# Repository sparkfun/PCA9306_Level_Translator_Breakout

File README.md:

PCA9306 Level Translator Breakout
=================================

[*PCA9306 Level Translator Breakout(BOB-15439)*](https://www.sparkfun.com/products/15439)

This is a breakout board for the PCA9306 dual bidirectional voltage-level translator. 

Repository Contents
-------------------
* **/Hardware** - Eagle design files for the board (.brd, .sch)

Documentation
--------------
* **[Hookup Guide](https://learn.sparkfun.com/tutorials/pca9306-logic-level-translator-hookup-guide-v2)** - Basic hookup guide for the PCA9306 logic level translator.
* **[Logic Levels](https://learn.sparkfun.com/tutorials/logic-levels)**
* **[SparkFun Fritzing repo](https://github.com/sparkfun/Fritzing_Parts)** - Fritzing diagrams for SparkFun products.

License Information
-------------------
The hardware is released under [Creative Commons Share-alike 3.0](http://creativecommons.org/licenses/by-sa/3.0/).

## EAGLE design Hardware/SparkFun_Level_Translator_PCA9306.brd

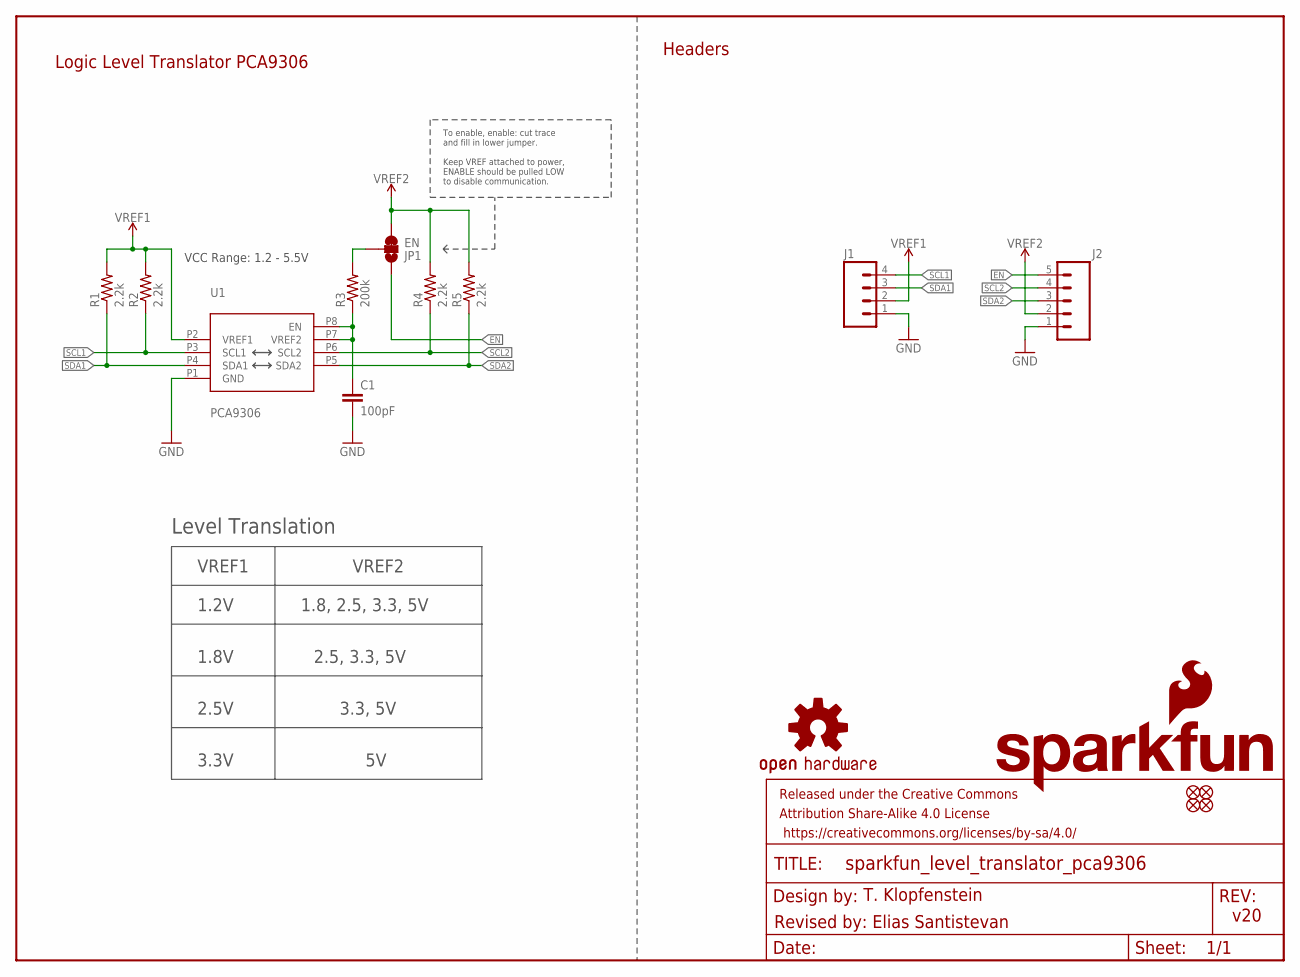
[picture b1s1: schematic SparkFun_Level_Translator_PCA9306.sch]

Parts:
C1: 100pF; 0603
FD1, FD2, FD3, FD4: FIDUCIALUFIDUCIAL; FIDUCIAL-MICRO
FRAME1: FRAME-LETTER; CREATIVE_COMMONS
J1: CONN_041X04_NO_SILK; 1X04_NO_SILK
J2: CONN_05NO_SILK; 1X05_NO_SILK
JP1: EN; SMT-JUMPER_3_1-NC_TRACE_SILK
LOGO1: OSHW-LOGOMINI; OSHW-LOGO-MINI
LOGO2: SFE_LOGO_NAME.1_INCH; SFE_LOGO_NAME_.1
LOGO3: SFE_LOGO_FLAME.1_INCH; SFE_LOGO_FLAME_.1
R1, R2, R4, R5: 2.2k; 0603
R3: 200k; 0603
U1: PCA9306; VSSOP_8PIN

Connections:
EN: J2.5, JP1.1
GND: C1.2, J1.1, J2.1, U1.P1 (GND)
JUMPER_IN: JP1.2, R3.2
SCL1: J1.4, R2.1, U1.P3 (SCL1)
SCL2: J2.4, R4.1, U1.P6 (SCL2)
SDA1: J1.3, R1.1, U1.P4 (SDA1)
SDA2: J2.3, R5.1, U1.P5 (SDA2)
VREF1: J1.2, R1.2, R2.2, U1.P2 (VREF1)
VREF2: J2.2, JP1.3, R4.2, R5.2
VREF2_IN: C1.1, R3.1, U1.P7 (VREF2), U1.P8 (EN)

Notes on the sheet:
T. Klopfenstein
v20
Logic Level Translator PCA9306
Headers
Revised by: Elias Santistevan
Level Translation
VREF1
VREF2
1.2V
1.8, 2.5, 3.3, 5V
1.8V
2.5, 3.3, 5V
2.5V
3.3, 5V
3.3V
VCC Range: 1.2 - 5.5V
To enable, enable: cut trace and fill in lower jumper.
Keep VREF attached to power, ENABLE should be pulled LOW to disable communication.

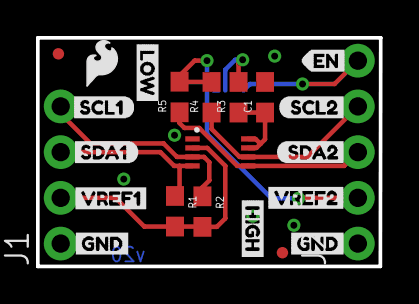
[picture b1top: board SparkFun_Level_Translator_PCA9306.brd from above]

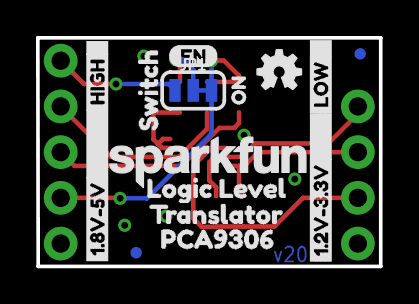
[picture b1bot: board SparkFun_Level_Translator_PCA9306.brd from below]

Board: 2 copper layers, 19.1 x 12.7 mm, 39 parts (15 on the bottom side), 10 nets.

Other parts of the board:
U$1: SWITCH1
U$2: VREF13
U$3: SCL11
U$4: SDA10
U$5, U$11: GND2
U$6: VREF20
U$7: SCL20
U$8: SDA21
U$9: EN0
U$10: EN1
U$12: LOGIC_LEVEL0
U$13: TRANSLATOR1
U$14: PCA93062
U$15: ON2
U$17, U$19: HIGH0
U$18, U$20: LOW1
U$21: 1#2V#3#3V0
U$22: 1#8V#5V1

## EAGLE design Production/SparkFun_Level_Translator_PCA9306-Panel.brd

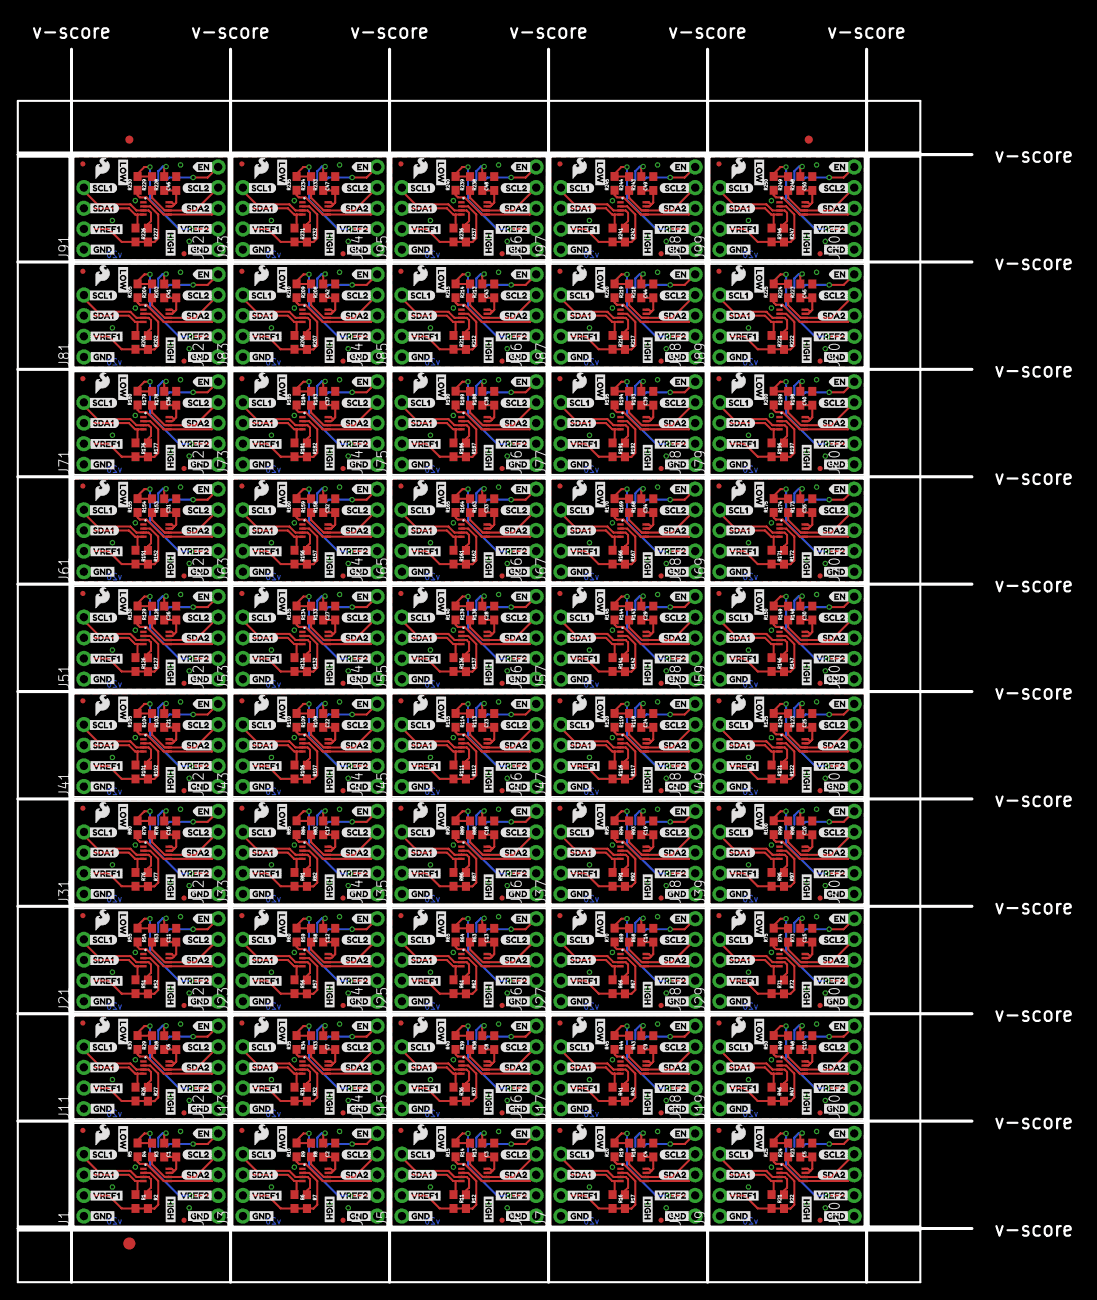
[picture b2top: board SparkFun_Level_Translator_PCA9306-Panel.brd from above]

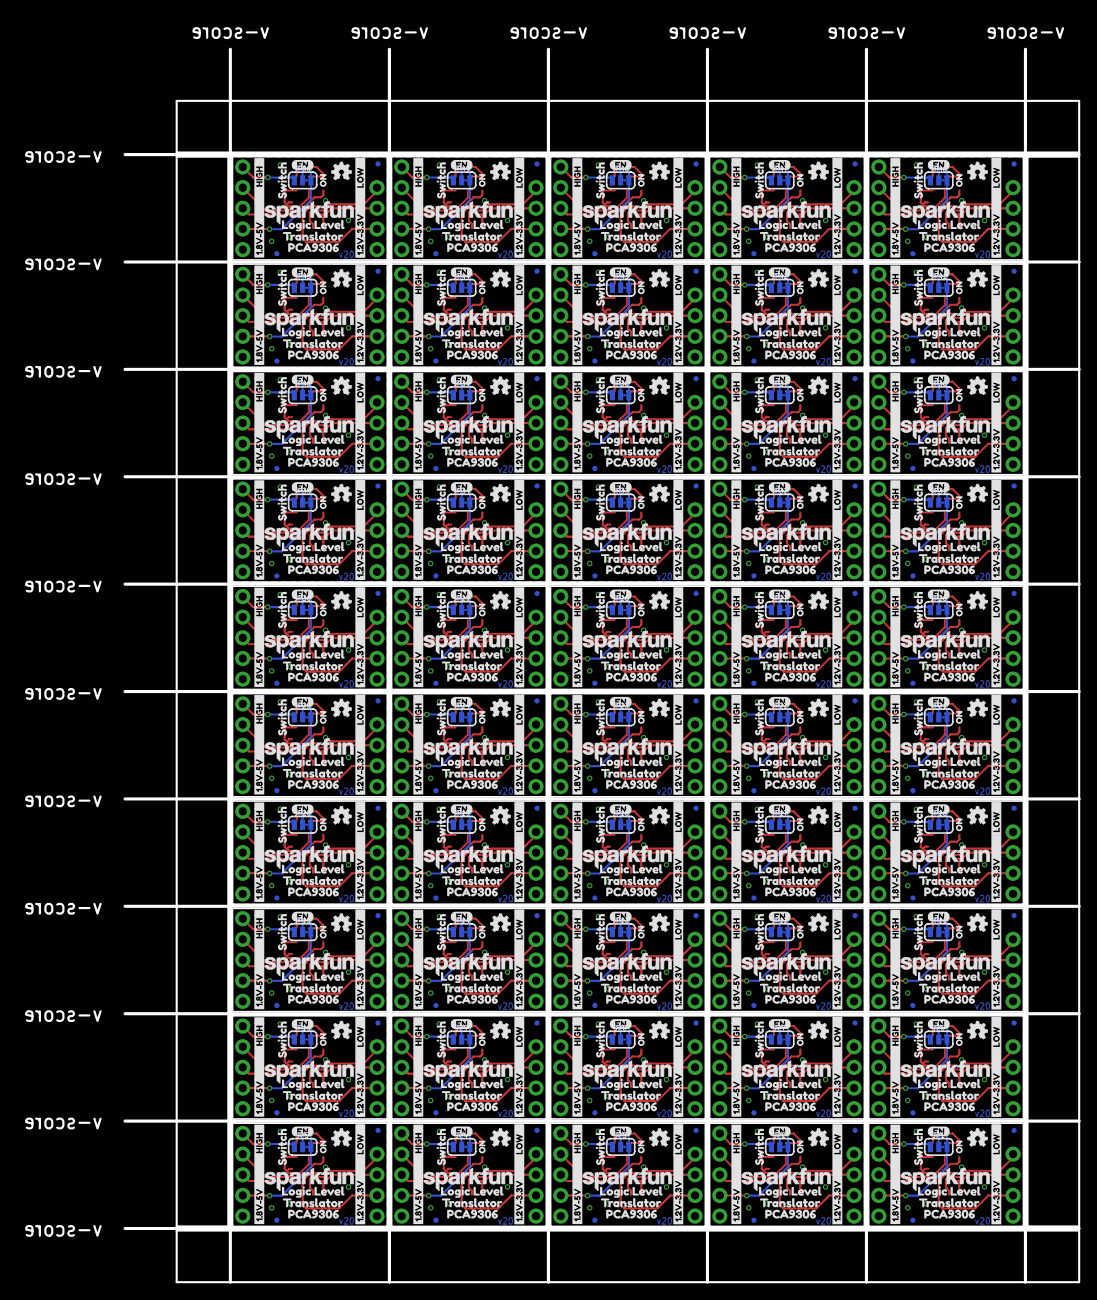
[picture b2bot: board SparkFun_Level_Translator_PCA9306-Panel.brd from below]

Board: 2 copper layers, 117.3 x 151.6 mm, 1903 parts (750 on the bottom side), 500 nets.

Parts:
C1, C2, C3, C4, C5, C6, C7, C8, C9, C10, C11, C12, C13, C14, C15, C16, C17, C18, C19, C20, C21, C22, C23, C24, C25, C26, C27, C28, C29, C30, C31, C32, C33, C34, C35, C36, C37, C38, C39, C40, C41, C42, C43, C44, C45, C46, C47, C48, C49, C50: 100pF; 0603
E$1, E$2: FIDUCIAL-1X2
E$3: FIDUCIAL-1.5X3
FD1, FD2, FD3, FD4, FD5, FD6, FD7, FD8, FD9, FD10, FD11, FD12, FD13, FD14, FD15, FD16, FD17, FD18, FD19, FD20, FD21, FD22, FD23, FD24, FD25, FD26, FD27, FD28, FD29, FD30, FD31, FD32, FD33, FD34, FD35, FD36, FD37, FD38, FD39, FD40, FD41, FD42, FD43, FD44, FD45, FD46, FD47, FD48, FD49, FD50, FD51, FD52, FD53, FD54, FD55, FD56, FD57, FD58, FD59, FD60, FD61, FD62, FD63, FD64, FD65, FD66, FD67, FD68, FD69, FD70, FD71, FD72, FD73, FD74, FD75, FD76, FD77, FD78, FD79, FD80, FD81, FD82, FD83, FD84, FD85, FD86, FD87, FD88, FD89, FD90, FD91, FD92, FD93, FD94, FD95, FD96, FD97, FD98, FD99, FD100, FD101, FD102, FD103, FD104, FD105, FD106, FD107, FD108, FD109, FD110, FD111, FD112, FD113, FD114, FD115, FD116, FD117, FD118, FD119, FD120, FD121, FD122, FD123, FD124, FD125, FD126, FD127, FD128, FD129, FD130, FD131, FD132, FD133, FD134, FD135, FD136, FD137, FD138, FD139, FD140, FD141, FD142, FD143, FD144, FD145, FD146, FD147, FD148, FD149, FD150, FD151, FD152, FD153, FD154, FD155, FD156, FD157, FD158, FD159, FD160, FD161, FD162, FD163, FD164, FD165, FD166, FD167, FD168, FD169, FD170, FD171, FD172, FD173, FD174, FD175, FD176, FD177, FD178, FD179, FD180, FD181, FD182, FD183, FD184, FD185, FD186, FD187, FD188, FD189, FD190, FD191, FD192, FD193, FD194, FD195, FD196, FD197, FD198, FD199, FD200: FIDUCIALUFIDUCIAL; FIDUCIAL-MICRO
J1, J3, J5, J7, J9, J11, J13, J15, J17, J19, J21, J23, J25, J27, J29, J31, J33, J35, J37, J39, J41, J43, J45, J47, J49, J51, J53, J55, J57, J59, J61, J63, J65, J67, J69, J71, J73, J75, J77, J79, J81, J83, J85, J87, J89, J91, J93, J95, J97, J99: 1X04_NO_SILK
J2, J4, J6, J8, J10, J12, J14, J16, J18, J20, J22, J24, J26, J28, J30, J32, J34, J36, J38, J40, J42, J44, J46, J48, J50, J52, J54, J56, J58, J60, J62, J64, J66, J68, J70, J72, J74, J76, J78, J80, J82, J84, J86, J88, J90, J92, J94, J96, J98, J100: 1X05_NO_SILK
JP1, JP2, JP3, JP4, JP5, JP6, JP7, JP8, JP9, JP10, JP11, JP12, JP13, JP14, JP15, JP16, JP17, JP18, JP19, JP20, JP21, JP22, JP23, JP24, JP25, JP26, JP27, JP28, JP29, JP30, JP31, JP32, JP33, JP34, JP35, JP36, JP37, JP38, JP39, JP40, JP41, JP42, JP43, JP44, JP45, JP46, JP47, JP48, JP49, JP50: EN; SMT-JUMPER_3_1-NC_TRACE_SILK
LOGO1, LOGO6, LOGO9, LOGO12, LOGO15, LOGO18, LOGO21, LOGO24, LOGO27, LOGO30, LOGO33, LOGO36, LOGO39, LOGO42, LOGO45, LOGO48, LOGO51, LOGO54, LOGO57, LOGO60, LOGO63, LOGO66, LOGO69, LOGO72, LOGO75, LOGO78, LOGO81, LOGO84, LOGO87, LOGO90, LOGO93, LOGO96, LOGO99, LOGO102, LOGO105, LOGO108, LOGO111, LOGO114, LOGO117, LOGO120, LOGO123, LOGO126, LOGO129, LOGO132, LOGO135, LOGO138, LOGO141, LOGO144, LOGO147, LOGO150: OSHW-LOGOMINI; OSHW-LOGO-MINI
LOGO2, LOGO5, LOGO8, LOGO11, LOGO14, LOGO17, LOGO20, LOGO23, LOGO26, LOGO29, LOGO32, LOGO35, LOGO38, LOGO41, LOGO44, LOGO47, LOGO50, LOGO53, LOGO56, LOGO59, LOGO62, LOGO65, LOGO68, LOGO71, LOGO74, LOGO77, LOGO80, LOGO83, LOGO86, LOGO89, LOGO92, LOGO95, LOGO98, LOGO101, LOGO104, LOGO107, LOGO110, LOGO113, LOGO116, LOGO119, LOGO122, LOGO125, LOGO128, LOGO131, LOGO134, LOGO137, LOGO140, LOGO143, LOGO146, LOGO149: SFE_LOGO_NAME.1_INCH; SFE_LOGO_NAME_.1
LOGO3, LOGO4, LOGO7, LOGO10, LOGO13, LOGO16, LOGO19, LOGO22, LOGO25, LOGO28, LOGO31, LOGO34, LOGO37, LOGO40, LOGO43, LOGO46, LOGO49, LOGO52, LOGO55, LOGO58, LOGO61, LOGO64, LOGO67, LOGO70, LOGO73, LOGO76, LOGO79, LOGO82, LOGO85, LOGO88, LOGO91, LOGO94, LOGO97, LOGO100, LOGO103, LOGO106, LOGO109, LOGO112, LOGO115, LOGO118, LOGO121, LOGO124, LOGO127, LOGO130, LOGO133, LOGO136, LOGO139, LOGO142, LOGO145, LOGO148: SFE_LOGO_FLAME.1_INCH; SFE_LOGO_FLAME_.1
R1, R2, R4, R5, R6, R7, R9, R10, R11, R12, R14, R15, R16, R17, R19, R20, R21, R22, R24, R25, R26, R27, R29, R30, R31, R32, R34, R35, R36, R37, R39, R40, R41, R42, R44, R45, R46, R47, R49, R50, R51, R52, R54, R55, R56, R57, R59, R60, R61, R62, R64, R65, R66, R67, R69, R70, R71, R72, R74, R75, R76, R77, R79, R80, R81, R82, R84, R85, R86, R87, R89, R90, R91, R92, R94, R95, R96, R97, R99, R100, R101, R102, R104, R105, R106, R107, R109, R110, R111, R112, R114, R115, R116, R117, R119, R120, R121, R122, R124, R125, R126, R127, R129, R130, R131, R132, R134, R135, R136, R137, R139, R140, R141, R142, R144, R145, R146, R147, R149, R150, R151, R152, R154, R155, R156, R157, R159, R160, R161, R162, R164, R165, R166, R167, R169, R170, R171, R172, R174, R175, R176, R177, R179, R180, R181, R182, R184, R185, R186, R187, R189, R190, R191, R192, R194, R195, R196, R197, R199, R200, R201, R202, R204, R205, R206, R207, R209, R210, R211, R212, R214, R215, R216, R217, R219, R220, R221, R222, R224, R225, R226, R227, R229, R230, R231, R232, R234, R235, R236, R237, R239, R240, R241, R242, R244, R245, R246, R247, R249, R250: 2.2k; 0603
R3, R8, R13, R18, R23, R28, R33, R38, R43, R48, R53, R58, R63, R68, R73, R78, R83, R88, R93, R98, R103, R108, R113, R118, R123, R128, R133, R138, R143, R148, R153, R158, R163, R168, R173, R178, R183, R188, R193, R198, R203, R208, R213, R218, R223, R228, R233, R238, R243, R248: 200k; 0603
U1, U2, U3, U4, U5, U6, U7, U8, U9, U10, U11, U12, U13, U14, U15, U16, U17, U18, U19, U20, U21, U22, U23, U24, U25, U26, U27, U28, U29, U30, U31, U32, U33, U34, U35, U36, U37, U38, U39, U40, U41, U42, U43, U44, U45, U46, U47, U48, U49, U50: PCA9306; VSSOP_8PIN
U$1, U$42, U$63, U$84, U$105, U$126, U$147, U$168, U$189, U$210, U$231, U$252, U$273, U$294, U$315, U$336, U$357, U$378, U$399, U$420, U$441, U$462, U$483, U$504, U$525, U$546, U$567, U$588, U$609, U$630, U$651, U$672, U$693, U$714, U$735, U$756, U$777, U$798, U$819, U$840, U$861, U$882, U$903, U$924, U$945, U$966, U$987, U$1008, U$1029, U$1050: SWITCH1
U$2, U$16, U$43, U$64, U$85, U$106, U$127, U$148, U$169, U$190, U$211, U$232, U$253, U$274, U$295, U$316, U$337, U$358, U$379, U$400, U$421, U$442, U$463, U$484, U$505, U$526, U$547, U$568, U$589, U$610, U$631, U$652, U$673, U$694, U$715, U$736, U$757, U$778, U$799, U$820, U$841, U$862, U$883, U$904, U$925, U$946, U$967, U$988, U$1009, U$1030: VREF13
U$3, U$23, U$44, U$65, U$86, U$107, U$128, U$149, U$170, U$191, U$212, U$233, U$254, U$275, U$296, U$317, U$338, U$359, U$380, U$401, U$422, U$443, U$464, U$485, U$506, U$527, U$548, U$569, U$590, U$611, U$632, U$653, U$674, U$695, U$716, U$737, U$758, U$779, U$800, U$821, U$842, U$863, U$884, U$905, U$926, U$947, U$968, U$989, U$1010, U$1031: SCL11
U$4, U$24, U$45, U$66, U$87, U$108, U$129, U$150, U$171, U$192, U$213, U$234, U$255, U$276, U$297, U$318, U$339, U$360, U$381, U$402, U$423, U$444, U$465, U$486, U$507, U$528, U$549, U$570, U$591, U$612, U$633, U$654, U$675, U$696, U$717, U$738, U$759, U$780, U$801, U$822, U$843, U$864, U$885, U$906, U$927, U$948, U$969, U$990, U$1011, U$1032: SDA10
U$5, U$11, U$25, U$33, U$46, U$54, U$67, U$75, U$88, U$96, U$109, U$117, U$130, U$138, U$151, U$159, U$172, U$180, U$193, U$201, U$214, U$222, U$235, U$243, U$256, U$264, U$277, U$285, U$298, U$306, U$319, U$327, U$340, U$348, U$361, U$369, U$382, U$390, U$403, U$411, U$424, U$432, U$445, U$453, U$466, U$474, U$487, U$495, U$508, U$516, U$529, U$537, U$550, U$558, U$571, U$579, U$592, U$600, U$613, U$621, U$634, U$642, U$655, U$663, U$676, U$684, U$697, U$705, U$718, U$726, U$739, U$747, U$760, U$768, U$781, U$789, U$802, U$810, U$823, U$831, U$844, U$852, U$865, U$873, U$886, U$894, U$907, U$915, U$928, U$936, U$949, U$957, U$970, U$978, U$991, U$999, U$1012, U$1020, U$1033, U$1041: GND2
U$6, U$26, U$47, U$68, U$89, U$110, U$131, U$152, U$173, U$194, U$215, U$236, U$257, U$278, U$299, U$320, U$341, U$362, U$383, U$404, U$425, U$446, U$467, U$488, U$509, U$530, U$551, U$572, U$593, U$614, U$635, U$656, U$677, U$698, U$719, U$740, U$761, U$782, U$803, U$824, U$845, U$866, U$887, U$908, U$929, U$950, U$971, U$992, U$1013, U$1034: VREF20
U$7, U$34, U$55, U$76, U$97, U$118, U$139, U$160, U$181, U$202, U$223, U$244, U$265, U$286, U$307, U$328, U$349, U$370, U$391, U$412, U$433, U$454, U$475, U$496, U$517, U$538, U$559, U$580, U$601, U$622, U$643, U$664, U$685, U$706, U$727, U$748, U$769, U$790, U$811, U$832, U$853, U$874, U$895, U$916, U$937, U$958, U$979, U$1000, U$1021, U$1042: SCL20
U$8, U$27, U$48, U$69, U$90, U$111, U$132, U$153, U$174, U$195, U$216, U$237, U$258, U$279, U$300, U$321, U$342, U$363, U$384, U$405, U$426, U$447, U$468, U$489, U$510, U$531, U$552, U$573, U$594, U$615, U$636, U$657, U$678, U$699, U$720, U$741, U$762, U$783, U$804, U$825, U$846, U$867, U$888, U$909, U$930, U$951, U$972, U$993, U$1014, U$1035: SDA21
U$9, U$28, U$49, U$70, U$91, U$112, U$133, U$154, U$175, U$196, U$217, U$238, U$259, U$280, U$301, U$322, U$343, U$364, U$385, U$406, U$427, U$448, U$469, U$490, U$511, U$532, U$553, U$574, U$595, U$616, U$637, U$658, U$679, U$700, U$721, U$742, U$763, U$784, U$805, U$826, U$847, U$868, U$889, U$910, U$931, U$952, U$973, U$994, U$1015, U$1036: EN0
U$10, U$29, U$50, U$71, U$92, U$113, U$134, U$155, U$176, U$197, U$218, U$239, U$260, U$281, U$302, U$323, U$344, U$365, U$386, U$407, U$428, U$449, U$470, U$491, U$512, U$533, U$554, U$575, U$596, U$617, U$638, U$659, U$680, U$701, U$722, U$743, U$764, U$785, U$806, U$827, U$848, U$869, U$890, U$911, U$932, U$953, U$974, U$995, U$1016, U$1037: EN1
U$12, U$30, U$51, U$72, U$93, U$114, U$135, U$156, U$177, U$198, U$219, U$240, U$261, U$282, U$303, U$324, U$345, U$366, U$387, U$408, U$429, U$450, U$471, U$492, U$513, U$534, U$555, U$576, U$597, U$618, U$639, U$660, U$681, U$702, U$723, U$744, U$765, U$786, U$807, U$828, U$849, U$870, U$891, U$912, U$933, U$954, U$975, U$996, U$1017, U$1038: LOGIC_LEVEL0
U$13, U$31, U$52, U$73, U$94, U$115, U$136, U$157, U$178, U$199, U$220, U$241, U$262, U$283, U$304, U$325, U$346, U$367, U$388, U$409, U$430, U$451, U$472, U$493, U$514, U$535, U$556, U$577, U$598, U$619, U$640, U$661, U$682, U$703, U$724, U$745, U$766, U$787, U$808, U$829, U$850, U$871, U$892, U$913, U$934, U$955, U$976, U$997, U$1018, U$1039: TRANSLATOR1
U$14, U$32, U$53, U$74, U$95, U$116, U$137, U$158, U$179, U$200, U$221, U$242, U$263, U$284, U$305, U$326, U$347, U$368, U$389, U$410, U$431, U$452, U$473, U$494, U$515, U$536, U$557, U$578, U$599, U$620, U$641, U$662, U$683, U$704, U$725, U$746, U$767, U$788, U$809, U$830, U$851, U$872, U$893, U$914, U$935, U$956, U$977, U$998, U$1019, U$1040: PCA93062
U$15, U$39, U$60, U$81, U$102, U$123, U$144, U$165, U$186, U$207, U$228, U$249, U$270, U$291, U$312, U$333, U$354, U$375, U$396, U$417, U$438, U$459, U$480, U$501, U$522, U$543, U$564, U$585, U$606, U$627, U$648, U$669, U$690, U$711, U$732, U$753, U$774, U$795, U$816, U$837, U$858, U$879, U$900, U$921, U$942, U$963, U$984, U$1005, U$1026, U$1047: ON2
U$17, U$19, U$35, U$37, U$56, U$58, U$77, U$79, U$98, U$100, U$119, U$121, U$140, U$142, U$161, U$163, U$182, U$184, U$203, U$205, U$224, U$226, U$245, U$247, U$266, U$268, U$287, U$289, U$308, U$310, U$329, U$331, U$350, U$352, U$371, U$373, U$392, U$394, U$413, U$415, U$434, U$436, U$455, U$457, U$476, U$478, U$497, U$499, U$518, U$520, U$539, U$541, U$560, U$562, U$581, U$583, U$602, U$604, U$623, U$625, U$644, U$646, U$665, U$667, U$686, U$688, U$707, U$709, U$728, U$730, U$749, U$751, U$770, U$772, U$791, U$793, U$812, U$814, U$833, U$835, U$854, U$856, U$875, U$877, U$896, U$898, U$917, U$919, U$938, U$940, U$959, U$961, U$980, U$982, U$1001, U$1003, U$1022, U$1024, U$1043, U$1045: HIGH0
U$18, U$20, U$36, U$38, U$57, U$59, U$78, U$80, U$99, U$101, U$120, U$122, U$141, U$143, U$162, U$164, U$183, U$185, U$204, U$206, U$225, U$227, U$246, U$248, U$267, U$269, U$288, U$290, U$309, U$311, U$330, U$332, U$351, U$353, U$372, U$374, U$393, U$395, U$414, U$416, U$435, U$437, U$456, U$458, U$477, U$479, U$498, U$500, U$519, U$521, U$540, U$542, U$561, U$563, U$582, U$584, U$603, U$605, U$624, U$626, U$645, U$647, U$666, U$668, U$687, U$689, U$708, U$710, U$729, U$731, U$750, U$752, U$771, U$773, U$792, U$794, U$813, U$815, U$834, U$836, U$855, U$857, U$876, U$878, U$897, U$899, U$918, U$920, U$939, U$941, U$960, U$962, U$981, U$983, U$1002, U$1004, U$1023, U$1025, U$1044, U$1046: LOW1
U$21, U$40, U$61, U$82, U$103, U$124, U$145, U$166, U$187, U$208, U$229, U$250, U$271, U$292, U$313, U$334, U$355, U$376, U$397, U$418, U$439, U$460, U$481, U$502, U$523, U$544, U$565, U$586, U$607, U$628, U$649, U$670, U$691, U$712, U$733, U$754, U$775, U$796, U$817, U$838, U$859, U$880, U$901, U$922, U$943, U$964, U$985, U$1006, U$1027, U$1048: 1#2V#3#3V0
U$22, U$41, U$62, U$83, U$104, U$125, U$146, U$167, U$188, U$209, U$230, U$251, U$272, U$293, U$314, U$335, U$356, U$377, U$398, U$419, U$440, U$461, U$482, U$503, U$524, U$545, U$566, U$587, U$608, U$629, U$650, U$671, U$692, U$713, U$734, U$755, U$776, U$797, U$818, U$839, U$860, U$881, U$902, U$923, U$944, U$965, U$986, U$1007, U$1028, U$1049: 1#8V#5V1

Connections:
EN: J2.5, JP1.1
EN1: J4.5, JP2.1
EN2: J6.5, JP3.1
EN3: J8.5, JP4.1
EN4: J10.5, JP5.1
EN5: J12.5, JP6.1
EN6: J14.5, JP7.1
EN7: J16.5, JP8.1
EN8: J18.5, JP9.1
EN9: J20.5, JP10.1
EN10: J22.5, JP11.1
EN11: J24.5, JP12.1
EN12: J26.5, JP13.1
EN13: J28.5, JP14.1
EN14: J30.5, JP15.1
EN15: J32.5, JP16.1
EN16: J34.5, JP17.1
EN17: J36.5, JP18.1
EN18: J38.5, JP19.1
EN19: J40.5, JP20.1
EN20: J42.5, JP21.1
EN21: J44.5, JP22.1
EN22: J46.5, JP23.1
EN23: J48.5, JP24.1
EN24: J50.5, JP25.1
EN25: J52.5, JP26.1
EN26: J54.5, JP27.1
EN27: J56.5, JP28.1
EN28: J58.5, JP29.1
EN29: J60.5, JP30.1
EN30: J62.5, JP31.1
EN31: J64.5, JP32.1
EN32: J66.5, JP33.1
EN33: J68.5, JP34.1
EN34: J70.5, JP35.1
EN35: J72.5, JP36.1
EN36: J74.5, JP37.1
EN37: J76.5, JP38.1
EN38: J78.5, JP39.1
EN39: J80.5, JP40.1
EN40: J82.5, JP41.1
EN41: J84.5, JP42.1
EN42: J86.5, JP43.1
EN43: J88.5, JP44.1
EN44: J90.5, JP45.1
EN45: J92.5, JP46.1
EN46: J94.5, JP47.1
EN47: J96.5, JP48.1
EN48: J98.5, JP49.1
EN49: J100.5, JP50.1
GND: C1.2, J1.1, J2.1, U1.P1
GND1: C2.2, J3.1, J4.1, U2.P1
GND2: C3.2, J5.1, J6.1, U3.P1
GND3: C4.2, J7.1, J8.1, U4.P1
GND4: C5.2, J9.1, J10.1, U5.P1
GND5: C6.2, J11.1, J12.1, U6.P1
GND6: C7.2, J13.1, J14.1, U7.P1
GND7: C8.2, J15.1, J16.1, U8.P1
GND8: C9.2, J17.1, J18.1, U9.P1
GND9: C10.2, J19.1, J20.1, U10.P1
GND10: C11.2, J21.1, J22.1, U11.P1
GND11: C12.2, J23.1, J24.1, U12.P1
GND12: C13.2, J25.1, J26.1, U13.P1
GND13: C14.2, J27.1, J28.1, U14.P1
GND14: C15.2, J29.1, J30.1, U15.P1
GND15: C16.2, J31.1, J32.1, U16.P1
GND16: C17.2, J33.1, J34.1, U17.P1
GND17: C18.2, J35.1, J36.1, U18.P1
GND18: C19.2, J37.1, J38.1, U19.P1
GND19: C20.2, J39.1, J40.1, U20.P1
GND20: C21.2, J41.1, J42.1, U21.P1
GND21: C22.2, J43.1, J44.1, U22.P1
GND22: C23.2, J45.1, J46.1, U23.P1
GND23: C24.2, J47.1, J48.1, U24.P1
GND24: C25.2, J49.1, J50.1, U25.P1
GND25: C26.2, J51.1, J52.1, U26.P1
GND26: C27.2, J53.1, J54.1, U27.P1
GND27: C28.2, J55.1, J56.1, U28.P1
GND28: C29.2, J57.1, J58.1, U29.P1
GND29: C30.2, J59.1, J60.1, U30.P1
GND30: C31.2, J61.1, J62.1, U31.P1
GND31: C32.2, J63.1, J64.1, U32.P1
GND32: C33.2, J65.1, J66.1, U33.P1
GND33: C34.2, J67.1, J68.1, U34.P1
GND34: C35.2, J69.1, J70.1, U35.P1
GND35: C36.2, J71.1, J72.1, U36.P1
GND36: C37.2, J73.1, J74.1, U37.P1
GND37: C38.2, J75.1, J76.1, U38.P1
GND38: C39.2, J77.1, J78.1, U39.P1
GND39: C40.2, J79.1, J80.1, U40.P1
GND40: C41.2, J81.1, J82.1, U41.P1
GND41: C42.2, J83.1, J84.1, U42.P1
GND42: C43.2, J85.1, J86.1, U43.P1
GND43: C44.2, J87.1, J88.1, U44.P1
GND44: C45.2, J89.1, J90.1, U45.P1
GND45: C46.2, J91.1, J92.1, U46.P1
GND46: C47.2, J93.1, J94.1, U47.P1
GND47: C48.2, J95.1, J96.1, U48.P1
GND48: C49.2, J97.1, J98.1, U49.P1
GND49: C50.2, J99.1, J100.1, U50.P1
JUMPER_IN: JP1.2, R3.2
JUMPER_IN1: JP2.2, R8.2
JUMPER_IN2: JP3.2, R13.2
JUMPER_IN3: JP4.2, R18.2
JUMPER_IN4: JP5.2, R23.2
JUMPER_IN5: JP6.2, R28.2
JUMPER_IN6: JP7.2, R33.2
JUMPER_IN7: JP8.2, R38.2
JUMPER_IN8: JP9.2, R43.2
JUMPER_IN9: JP10.2, R48.2
JUMPER_IN10: JP11.2, R53.2
JUMPER_IN11: JP12.2, R58.2
JUMPER_IN12: JP13.2, R63.2
JUMPER_IN13: JP14.2, R68.2
JUMPER_IN14: JP15.2, R73.2
JUMPER_IN15: JP16.2, R78.2
JUMPER_IN16: JP17.2, R83.2
JUMPER_IN17: JP18.2, R88.2
JUMPER_IN18: JP19.2, R93.2
JUMPER_IN19: JP20.2, R98.2
JUMPER_IN20: JP21.2, R103.2
JUMPER_IN21: JP22.2, R108.2
JUMPER_IN22: JP23.2, R113.2
JUMPER_IN23: JP24.2, R118.2
JUMPER_IN24: JP25.2, R123.2
JUMPER_IN25: JP26.2, R128.2
JUMPER_IN26: JP27.2, R133.2
JUMPER_IN27: JP28.2, R138.2
JUMPER_IN28: JP29.2, R143.2
JUMPER_IN29: JP30.2, R148.2
JUMPER_IN30: JP31.2, R153.2
JUMPER_IN31: JP32.2, R158.2
JUMPER_IN32: JP33.2, R163.2
JUMPER_IN33: JP34.2, R168.2
JUMPER_IN34: JP35.2, R173.2
JUMPER_IN35: JP36.2, R178.2
JUMPER_IN36: JP37.2, R183.2
JUMPER_IN37: JP38.2, R188.2
JUMPER_IN38: JP39.2, R193.2
JUMPER_IN39: JP40.2, R198.2
JUMPER_IN40: JP41.2, R203.2
JUMPER_IN41: JP42.2, R208.2
JUMPER_IN42: JP43.2, R213.2
JUMPER_IN43: JP44.2, R218.2
JUMPER_IN44: JP45.2, R223.2
JUMPER_IN45: JP46.2, R228.2
JUMPER_IN46: JP47.2, R233.2
JUMPER_IN47: JP48.2, R238.2
JUMPER_IN48: JP49.2, R243.2
JUMPER_IN49: JP50.2, R248.2
SCL1: J1.4, R2.1, U1.P3
SCL2: J2.4, R4.1, U1.P6
SCL3: J3.4, R7.1, U2.P3
SCL4: J4.4, R9.1, U2.P6
SCL5: J5.4, R12.1, U3.P3
SCL6: J6.4, R14.1, U3.P6
SCL7: J7.4, R17.1, U4.P3
SCL8: J8.4, R19.1, U4.P6
SCL9: J9.4, R22.1, U5.P3
SCL10: J10.4, R24.1, U5.P6
SCL11: J11.4, R27.1, U6.P3
SCL12: J12.4, R29.1, U6.P6
SCL13: J13.4, R32.1, U7.P3
SCL14: J14.4, R34.1, U7.P6
SCL15: J15.4, R37.1, U8.P3
SCL16: J16.4, R39.1, U8.P6
SCL17: J17.4, R42.1, U9.P3
SCL18: J18.4, R44.1, U9.P6
SCL19: J19.4, R47.1, U10.P3
SCL20: J20.4, R49.1, U10.P6
SCL21: J21.4, R52.1, U11.P3
SCL22: J22.4, R54.1, U11.P6
SCL23: J23.4, R57.1, U12.P3
SCL24: J24.4, R59.1, U12.P6
SCL25: J25.4, R62.1, U13.P3
SCL26: J26.4, R64.1, U13.P6
SCL27: J27.4, R67.1, U14.P3
SCL28: J28.4, R69.1, U14.P6
SCL29: J29.4, R72.1, U15.P3
SCL30: J30.4, R74.1, U15.P6
SCL31: J31.4, R77.1, U16.P3
SCL32: J32.4, R79.1, U16.P6
SCL33: J33.4, R82.1, U17.P3
SCL34: J34.4, R84.1, U17.P6
SCL35: J35.4, R87.1, U18.P3
SCL36: J36.4, R89.1, U18.P6
SCL37: J37.4, R92.1, U19.P3
SCL38: J38.4, R94.1, U19.P6
SCL39: J39.4, R97.1, U20.P3
SCL40: J40.4, R99.1, U20.P6
SCL41: J41.4, R102.1, U21.P3
SCL42: J42.4, R104.1, U21.P6
SCL43: J43.4, R107.1, U22.P3
SCL44: J44.4, R109.1, U22.P6
SCL45: J45.4, R112.1, U23.P3
SCL46: J46.4, R114.1, U23.P6
SCL47: J47.4, R117.1, U24.P3
SCL48: J48.4, R119.1, U24.P6
SCL49: J49.4, R122.1, U25.P3
SCL50: J50.4, R124.1, U25.P6
SCL51: J51.4, R127.1, U26.P3
SCL52: J52.4, R129.1, U26.P6
SCL53: J53.4, R132.1, U27.P3
SCL54: J54.4, R134.1, U27.P6
SCL55: J55.4, R137.1, U28.P3
SCL56: J56.4, R139.1, U28.P6
SCL57: J57.4, R142.1, U29.P3
SCL58: J58.4, R144.1, U29.P6
SCL59: J59.4, R147.1, U30.P3
SCL60: J60.4, R149.1, U30.P6
SCL61: J61.4, R152.1, U31.P3
SCL62: J62.4, R154.1, U31.P6
SCL63: J63.4, R157.1, U32.P3
SCL64: J64.4, R159.1, U32.P6
SCL65: J65.4, R162.1, U33.P3
SCL66: J66.4, R164.1, U33.P6
SCL67: J67.4, R167.1, U34.P3
SCL68: J68.4, R169.1, U34.P6
SCL69: J69.4, R172.1, U35.P3
SCL70: J70.4, R174.1, U35.P6
SCL71: J71.4, R177.1, U36.P3
SCL72: J72.4, R179.1, U36.P6
SCL73: J73.4, R182.1, U37.P3
SCL74: J74.4, R184.1, U37.P6
SCL75: J75.4, R187.1, U38.P3
SCL76: J76.4, R189.1, U38.P6
SCL77: J77.4, R192.1, U39.P3
SCL78: J78.4, R194.1, U39.P6
SCL79: J79.4, R197.1, U40.P3
SCL80: J80.4, R199.1, U40.P6
SCL81: J81.4, R202.1, U41.P3
SCL82: J82.4, R204.1, U41.P6
SCL83: J83.4, R207.1, U42.P3
SCL84: J84.4, R209.1, U42.P6
SCL85: J85.4, R212.1, U43.P3
SCL86: J86.4, R214.1, U43.P6
SCL87: J87.4, R217.1, U44.P3
SCL88: J88.4, R219.1, U44.P6
SCL89: J89.4, R222.1, U45.P3
SCL90: J90.4, R224.1, U45.P6
SCL91: J91.4, R227.1, U46.P3
SCL92: J92.4, R229.1, U46.P6
SCL93: J93.4, R232.1, U47.P3
SCL94: J94.4, R234.1, U47.P6
SCL95: J95.4, R237.1, U48.P3
SCL96: J96.4, R239.1, U48.P6
SCL97: J97.4, R242.1, U49.P3
SCL98: J98.4, R244.1, U49.P6
SCL99: J99.4, R247.1, U50.P3
SCL100: J100.4, R249.1, U50.P6
SDA1: J1.3, R1.1, U1.P4
SDA2: J2.3, R5.1, U1.P5
SDA3: J3.3, R6.1, U2.P4
SDA4: J4.3, R10.1, U2.P5
SDA5: J5.3, R11.1, U3.P4
SDA6: J6.3, R15.1, U3.P5
SDA7: J7.3, R16.1, U4.P4
SDA8: J8.3, R20.1, U4.P5
SDA9: J9.3, R21.1, U5.P4
SDA10: J10.3, R25.1, U5.P5
SDA11: J11.3, R26.1, U6.P4
SDA12: J12.3, R30.1, U6.P5
SDA13: J13.3, R31.1, U7.P4
SDA14: J14.3, R35.1, U7.P5
SDA15: J15.3, R36.1, U8.P4
SDA16: J16.3, R40.1, U8.P5
SDA17: J17.3, R41.1, U9.P4
SDA18: J18.3, R45.1, U9.P5
SDA19: J19.3, R46.1, U10.P4
SDA20: J20.3, R50.1, U10.P5
SDA21: J21.3, R51.1, U11.P4
SDA22: J22.3, R55.1, U11.P5
SDA23: J23.3, R56.1, U12.P4
SDA24: J24.3, R60.1, U12.P5
SDA25: J25.3, R61.1, U13.P4
SDA26: J26.3, R65.1, U13.P5
SDA27: J27.3, R66.1, U14.P4
SDA28: J28.3, R70.1, U14.P5
SDA29: J29.3, R71.1, U15.P4
SDA30: J30.3, R75.1, U15.P5
SDA31: J31.3, R76.1, U16.P4
SDA32: J32.3, R80.1, U16.P5
SDA33: J33.3, R81.1, U17.P4
SDA34: J34.3, R85.1, U17.P5
SDA35: J35.3, R86.1, U18.P4
SDA36: J36.3, R90.1, U18.P5
SDA37: J37.3, R91.1, U19.P4
SDA38: J38.3, R95.1, U19.P5
SDA39: J39.3, R96.1, U20.P4
SDA40: J40.3, R100.1, U20.P5
SDA41: J41.3, R101.1, U21.P4
SDA42: J42.3, R105.1, U21.P5
SDA43: J43.3, R106.1, U22.P4
SDA44: J44.3, R110.1, U22.P5
SDA45: J45.3, R111.1, U23.P4
SDA46: J46.3, R115.1, U23.P5
SDA47: J47.3, R116.1, U24.P4
SDA48: J48.3, R120.1, U24.P5
SDA49: J49.3, R121.1, U25.P4
SDA50: J50.3, R125.1, U25.P5
SDA51: J51.3, R126.1, U26.P4
SDA52: J52.3, R130.1, U26.P5
SDA53: J53.3, R131.1, U27.P4
SDA54: J54.3, R135.1, U27.P5
SDA55: J55.3, R136.1, U28.P4
SDA56: J56.3, R140.1, U28.P5
SDA57: J57.3, R141.1, U29.P4
SDA58: J58.3, R145.1, U29.P5
SDA59: J59.3, R146.1, U30.P4
SDA60: J60.3, R150.1, U30.P5
SDA61: J61.3, R151.1, U31.P4
SDA62: J62.3, R155.1, U31.P5
SDA63: J63.3, R156.1, U32.P4
SDA64: J64.3, R160.1, U32.P5
SDA65: J65.3, R161.1, U33.P4
SDA66: J66.3, R165.1, U33.P5
SDA67: J67.3, R166.1, U34.P4
SDA68: J68.3, R170.1, U34.P5
SDA69: J69.3, R171.1, U35.P4
SDA70: J70.3, R175.1, U35.P5
SDA71: J71.3, R176.1, U36.P4
SDA72: J72.3, R180.1, U36.P5
SDA73: J73.3, R181.1, U37.P4
SDA74: J74.3, R185.1, U37.P5
SDA75: J75.3, R186.1, U38.P4
SDA76: J76.3, R190.1, U38.P5
SDA77: J77.3, R191.1, U39.P4
SDA78: J78.3, R195.1, U39.P5
SDA79: J79.3, R196.1, U40.P4
SDA80: J80.3, R200.1, U40.P5
SDA81: J81.3, R201.1, U41.P4
SDA82: J82.3, R205.1, U41.P5
SDA83: J83.3, R206.1, U42.P4
SDA84: J84.3, R210.1, U42.P5
SDA85: J85.3, R211.1, U43.P4
SDA86: J86.3, R215.1, U43.P5
SDA87: J87.3, R216.1, U44.P4
SDA88: J88.3, R220.1, U44.P5
SDA89: J89.3, R221.1, U45.P4
SDA90: J90.3, R225.1, U45.P5
SDA91: J91.3, R226.1, U46.P4
SDA92: J92.3, R230.1, U46.P5
SDA93: J93.3, R231.1, U47.P4
SDA94: J94.3, R235.1, U47.P5
SDA95: J95.3, R236.1, U48.P4
SDA96: J96.3, R240.1, U48.P5
SDA97: J97.3, R241.1, U49.P4
SDA98: J98.3, R245.1, U49.P5
SDA99: J99.3, R246.1, U50.P4
SDA100: J100.3, R250.1, U50.P5
VREF1: J1.2, R1.2, R2.2, U1.P2
VREF2: J2.2, JP1.3, R4.2, R5.2
VREF2_IN: C1.1, R3.1, U1.P7, U1.P8
VREF2_IN1: C2.1, R8.1, U2.P7, U2.P8
VREF2_IN2: C3.1, R13.1, U3.P7, U3.P8
VREF2_IN3: C4.1, R18.1, U4.P7, U4.P8
VREF2_IN4: C5.1, R23.1, U5.P7, U5.P8
VREF2_IN5: C6.1, R28.1, U6.P7, U6.P8
VREF2_IN6: C7.1, R33.1, U7.P7, U7.P8
VREF2_IN7: C8.1, R38.1, U8.P7, U8.P8
VREF2_IN8: C9.1, R43.1, U9.P7, U9.P8
VREF2_IN9: C10.1, R48.1, U10.P7, U10.P8
VREF2_IN10: C11.1, R53.1, U11.P7, U11.P8
VREF2_IN11: C12.1, R58.1, U12.P7, U12.P8
VREF2_IN12: C13.1, R63.1, U13.P7, U13.P8
VREF2_IN13: C14.1, R68.1, U14.P7, U14.P8
VREF2_IN14: C15.1, R73.1, U15.P7, U15.P8
VREF2_IN15: C16.1, R78.1, U16.P7, U16.P8
VREF2_IN16: C17.1, R83.1, U17.P7, U17.P8
VREF2_IN17: C18.1, R88.1, U18.P7, U18.P8
VREF2_IN18: C19.1, R93.1, U19.P7, U19.P8
VREF2_IN19: C20.1, R98.1, U20.P7, U20.P8
VREF2_IN20: C21.1, R103.1, U21.P7, U21.P8
VREF2_IN21: C22.1, R108.1, U22.P7, U22.P8
VREF2_IN22: C23.1, R113.1, U23.P7, U23.P8
VREF2_IN23: C24.1, R118.1, U24.P7, U24.P8
VREF2_IN24: C25.1, R123.1, U25.P7, U25.P8
VREF2_IN25: C26.1, R128.1, U26.P7, U26.P8
VREF2_IN26: C27.1, R133.1, U27.P7, U27.P8
VREF2_IN27: C28.1, R138.1, U28.P7, U28.P8
VREF2_IN28: C29.1, R143.1, U29.P7, U29.P8
VREF2_IN29: C30.1, R148.1, U30.P7, U30.P8
VREF2_IN30: C31.1, R153.1, U31.P7, U31.P8
VREF2_IN31: C32.1, R158.1, U32.P7, U32.P8
VREF2_IN32: C33.1, R163.1, U33.P7, U33.P8
VREF2_IN33: C34.1, R168.1, U34.P7, U34.P8
VREF2_IN34: C35.1, R173.1, U35.P7, U35.P8
VREF2_IN35: C36.1, R178.1, U36.P7, U36.P8
VREF2_IN36: C37.1, R183.1, U37.P7, U37.P8
VREF2_IN37: C38.1, R188.1, U38.P7, U38.P8
VREF2_IN38: C39.1, R193.1, U39.P7, U39.P8
VREF2_IN39: C40.1, R198.1, U40.P7, U40.P8
VREF2_IN40: C41.1, R203.1, U41.P7, U41.P8
VREF2_IN41: C42.1, R208.1, U42.P7, U42.P8
VREF2_IN42: C43.1, R213.1, U43.P7, U43.P8
VREF2_IN43: C44.1, R218.1, U44.P7, U44.P8
VREF2_IN44: C45.1, R223.1, U45.P7, U45.P8
VREF2_IN45: C46.1, R228.1, U46.P7, U46.P8
VREF2_IN46: C47.1, R233.1, U47.P7, U47.P8
VREF2_IN47: C48.1, R238.1, U48.P7, U48.P8
VREF2_IN48: C49.1, R243.1, U49.P7, U49.P8
VREF2_IN49: C50.1, R248.1, U50.P7, U50.P8
VREF3: J4.2, JP2.3, R9.2, R10.2
VREF4: J3.2, R6.2, R7.2, U2.P2
VREF5: J6.2, JP3.3, R14.2, R15.2
VREF6: J5.2, R11.2, R12.2, U3.P2
VREF7: J8.2, JP4.3, R19.2, R20.2
VREF8: J7.2, R16.2, R17.2, U4.P2
VREF9: J10.2, JP5.3, R24.2, R25.2
VREF10: J9.2, R21.2, R22.2, U5.P2
VREF11: J12.2, JP6.3, R29.2, R30.2
VREF12: J11.2, R26.2, R27.2, U6.P2
VREF13: J14.2, JP7.3, R34.2, R35.2
VREF14: J13.2, R31.2, R32.2, U7.P2
VREF15: J16.2, JP8.3, R39.2, R40.2
VREF16: J15.2, R36.2, R37.2, U8.P2
VREF17: J18.2, JP9.3, R44.2, R45.2
VREF18: J17.2, R41.2, R42.2, U9.P2
VREF19: J20.2, JP10.3, R49.2, R50.2
VREF20: J19.2, R46.2, R47.2, U10.P2
VREF21: J22.2, JP11.3, R54.2, R55.2
VREF22: J21.2, R51.2, R52.2, U11.P2
VREF23: J24.2, JP12.3, R59.2, R60.2
VREF24: J23.2, R56.2, R57.2, U12.P2
VREF25: J26.2, JP13.3, R64.2, R65.2
VREF26: J25.2, R61.2, R62.2, U13.P2
VREF27: J28.2, JP14.3, R69.2, R70.2
VREF28: J27.2, R66.2, R67.2, U14.P2
VREF29: J30.2, JP15.3, R74.2, R75.2
VREF30: J29.2, R71.2, R72.2, U15.P2
VREF31: J32.2, JP16.3, R79.2, R80.2
VREF32: J31.2, R76.2, R77.2, U16.P2
VREF33: J34.2, JP17.3, R84.2, R85.2
VREF34: J33.2, R81.2, R82.2, U17.P2
VREF35: J36.2, JP18.3, R89.2, R90.2
VREF36: J35.2, R86.2, R87.2, U18.P2
VREF37: J38.2, JP19.3, R94.2, R95.2
VREF38: J37.2, R91.2, R92.2, U19.P2
VREF39: J40.2, JP20.3, R99.2, R100.2
VREF40: J39.2, R96.2, R97.2, U20.P2
VREF41: J42.2, JP21.3, R104.2, R105.2
VREF42: J41.2, R101.2, R102.2, U21.P2
VREF43: J44.2, JP22.3, R109.2, R110.2
VREF44: J43.2, R106.2, R107.2, U22.P2
VREF45: J46.2, JP23.3, R114.2, R115.2
VREF46: J45.2, R111.2, R112.2, U23.P2
VREF47: J48.2, JP24.3, R119.2, R120.2
VREF48: J47.2, R116.2, R117.2, U24.P2
VREF49: J50.2, JP25.3, R124.2, R125.2
VREF50: J49.2, R121.2, R122.2, U25.P2
VREF51: J52.2, JP26.3, R129.2, R130.2
VREF52: J51.2, R126.2, R127.2, U26.P2
VREF53: J54.2, JP27.3, R134.2, R135.2
VREF54: J53.2, R131.2, R132.2, U27.P2
VREF55: J56.2, JP28.3, R139.2, R140.2
VREF56: J55.2, R136.2, R137.2, U28.P2
VREF57: J58.2, JP29.3, R144.2, R145.2
VREF58: J57.2, R141.2, R142.2, U29.P2
VREF59: J60.2, JP30.3, R149.2, R150.2
VREF60: J59.2, R146.2, R147.2, U30.P2
VREF61: J62.2, JP31.3, R154.2, R155.2
VREF62: J61.2, R151.2, R152.2, U31.P2
VREF63: J64.2, JP32.3, R159.2, R160.2
VREF64: J63.2, R156.2, R157.2, U32.P2
VREF65: J66.2, JP33.3, R164.2, R165.2
VREF66: J65.2, R161.2, R162.2, U33.P2
VREF67: J68.2, JP34.3, R169.2, R170.2
VREF68: J67.2, R166.2, R167.2, U34.P2
VREF69: J70.2, JP35.3, R174.2, R175.2
VREF70: J69.2, R171.2, R172.2, U35.P2
VREF71: J72.2, JP36.3, R179.2, R180.2
VREF72: J71.2, R176.2, R177.2, U36.P2
VREF73: J74.2, JP37.3, R184.2, R185.2
VREF74: J73.2, R181.2, R182.2, U37.P2
VREF75: J76.2, JP38.3, R189.2, R190.2
VREF76: J75.2, R186.2, R187.2, U38.P2
VREF77: J78.2, JP39.3, R194.2, R195.2
VREF78: J77.2, R191.2, R192.2, U39.P2
VREF79: J80.2, JP40.3, R199.2, R200.2
VREF80: J79.2, R196.2, R197.2, U40.P2
VREF81: J82.2, JP41.3, R204.2, R205.2
VREF82: J81.2, R201.2, R202.2, U41.P2
VREF83: J84.2, JP42.3, R209.2, R210.2
VREF84: J83.2, R206.2, R207.2, U42.P2
VREF85: J86.2, JP43.3, R214.2, R215.2
VREF86: J85.2, R211.2, R212.2, U43.P2
VREF87: J88.2, JP44.3, R219.2, R220.2
VREF88: J87.2, R216.2, R217.2, U44.P2
VREF89: J90.2, JP45.3, R224.2, R225.2
VREF90: J89.2, R221.2, R222.2, U45.P2
VREF91: J92.2, JP46.3, R229.2, R230.2
VREF92: J91.2, R226.2, R227.2, U46.P2
VREF93: J94.2, JP47.3, R234.2, R235.2
VREF94: J93.2, R231.2, R232.2, U47.P2
VREF95: J96.2, JP48.3, R239.2, R240.2
VREF96: J95.2, R236.2, R237.2, U48.P2
VREF97: J98.2, JP49.3, R244.2, R245.2
VREF98: J97.2, R241.2, R242.2, U49.P2
VREF99: J100.2, JP50.3, R249.2, R250.2
VREF100: J99.2, R246.2, R247.2, U50.P2

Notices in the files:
parts and their libraries:
SparkFun-Aesthetics: Licensing: CC v3.0 Share-Alike You are welcome to use this library for commercial purposes.
SparkFun-Aesthetics: Released under the Creative Commons Attribution Share-Alike 4.0 License
SparkFun-Aesthetics: https://creativecommons.org/licenses/by-sa/4.0
